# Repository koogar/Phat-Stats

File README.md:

Phat-Stats is an open-source Arduino project that transforms a TFT display into a real-time PC hardware performance monitor. Developed by Rupert Hirst and Colin Conway, it serves as a larger, color-enhanced counterpart to the Gnat-Stats OLED monitor, offering a visually rich interface for tracking system metrics.([GitHub][1], [GitHub][2])

---

### 🔧 Features

* **Real-Time Monitoring**: Displays key PC performance metrics such as CPU usage, temperatures, and more.
* **TFT Display Support**: Designed for ILI9341 TFT screens, providing a vibrant and detailed visual output.
* **Arduino Compatibility**: Supports various Arduino-compatible boards, including ESP32 and Seeeduino XIAO.
* **Windows Integration**: Utilizes the HardwareSerialMonitor Windows client to fetch and transmit system data via USB serial communication.([GitHub][1], [GitHub][3], [GitHub][4])

---

### 🛠️ Getting Started

1. **Hardware Setup**:

   * Connect an ILI9341 TFT display to your chosen Arduino-compatible board.
   * For detailed setup guides and tutorials, refer to the [Phat-Stats ILI9341 TFT Display Hook-Up Guide](https://runawaybrainz.blogspot.com/2021/03/phat-stats-ili9341-tft-display-hook-up.html).
    
2. **Software Installation**:

   * Flash the appropriate Phat-Stats firmware onto your microcontroller.
   * Install the [HardwareSerialMonitor](https://github.com/koogar/HardwareSerialMonitor) on your Windows PC to relay performance data.
3. **Configuration**:

   * Adjust settings within the Phat-Stats firmware and HardwareSerialMonitor to match your hardware setup and monitoring preferences.

---

### 📦 Repository Contents

* **Firmware Variants**:

  * `PhatStats_ESP32_LOLIN`: For ESP32-based boards.
  * `PhatStats_XIAO_QT-PY_WIO`: Tailored for Seeeduino XIAO and similar boards.

* **Documentation**:

  * `README.md`: Project overview and setup instructions.
  * `LICENSE.txt`: GPL v2 license details.([GitHub][1], [GitHub][3], [GitHub][2])

---

### 📄 License

Phat-Stats is released under the GNU General Public License v2.0. You are free to use, modify, and distribute this software in accordance with the license terms.

---

### 🔗 Additional Resources

* **Project Blog**: [Runaway Brainz](http://runawaybrainz.blogspot.com/)
* **Developer Site**: [Tallman Labs](http://tallmanlabs.com)
* **Related Projects**:

  * [Gnat-Stats](https://github.com/koogar/Gnat-Stats): A compact OLED-based performance monitor.
  * [Tacho-Stats](https://github.com/koogar/Tacho-Stats): Designed for Seeed Studio Round Displays.([GitHub][5], [GitHub][2], [GitHub][3])

---

For detailed setup guides and tutorials, refer to the [Phat-Stats ILI9341 TFT Display Hook-Up Guide](https://runawaybrainz.blogspot.com/2021/03/phat-stats-ili9341-tft-display-hook-up.html).

---

[1]: https://github.com/koogar/Phat-Stats?utm_source=chatgpt.com "GitHub - koogar/Phat-Stats: TFT Arduino PC Hardware Performance Serial ..."
[2]: https://github.com/koogar/Gnat-Stats?utm_source=chatgpt.com "GitHub - koogar/Gnat-Stats: GnatStats Tiny OLED Arduino PC Hardware ..."
[3]: https://github.com/koogar/Tacho-Stats?utm_source=chatgpt.com "GitHub - koogar/Tacho-Stats: PC Hardware Performance Monitor for the ..."
[4]: https://github.com/koogar/HardwareSerialMonitor?utm_source=chatgpt.com "GitHub - koogar/HardwareSerialMonitor: PC Performance Stats Serial ..."
[5]: https://github.com/koogar?utm_source=chatgpt.com "koogar (Tallman Labs) - GitHub"

  #GNATSTATS OLED, PHATSTATS TFT PC Performance Monitor & HardwareSerialMonitor Windows Client  
   Rupert Hirst & Colin Conway © 2016-2025

 http://tallmanlabs.com
 http://runawaybrainz.blogspot.com/  
 https://hackaday.io/project/19018-phat-stats-pc-performance-tft-display

# Phat-Stats TFT
 Arduino PC Hardware Performance Serial Display
Phat-Stats ILI9341 TFT

https://runawaybrainz.blogspot.com/2021/03/phat-stats-ili9341-tft-display-hook-up.html

.jpg)

.jpg)

  Licence
  -------
  
  GPL v2
  
Gnat-Stats, Phat-Stats, Tacho-Stats, uVolume & HardwareSerialMonitor
Copyright (C) 2016 -2025  Colin Conway, Rupert Hirst and contributors
 
This program is free software; you can redistribute it and/or
modify it under the terms of the GNU General Public License
as published by the Free Software Foundation; either version 2
of the License, or (at your option) any later version.

This program is distributed in the hope that it will be useful,
but WITHOUT ANY WARRANTY; without even the implied warranty of
MERCHANTABILITY or FITNESS FOR A PARTICULAR PURPOSE.  See the
GNU General Public License for more details.

You should have received a copy of the GNU General Public License
along with this program; If not, see <http://www.gnu.org/licenses/>.

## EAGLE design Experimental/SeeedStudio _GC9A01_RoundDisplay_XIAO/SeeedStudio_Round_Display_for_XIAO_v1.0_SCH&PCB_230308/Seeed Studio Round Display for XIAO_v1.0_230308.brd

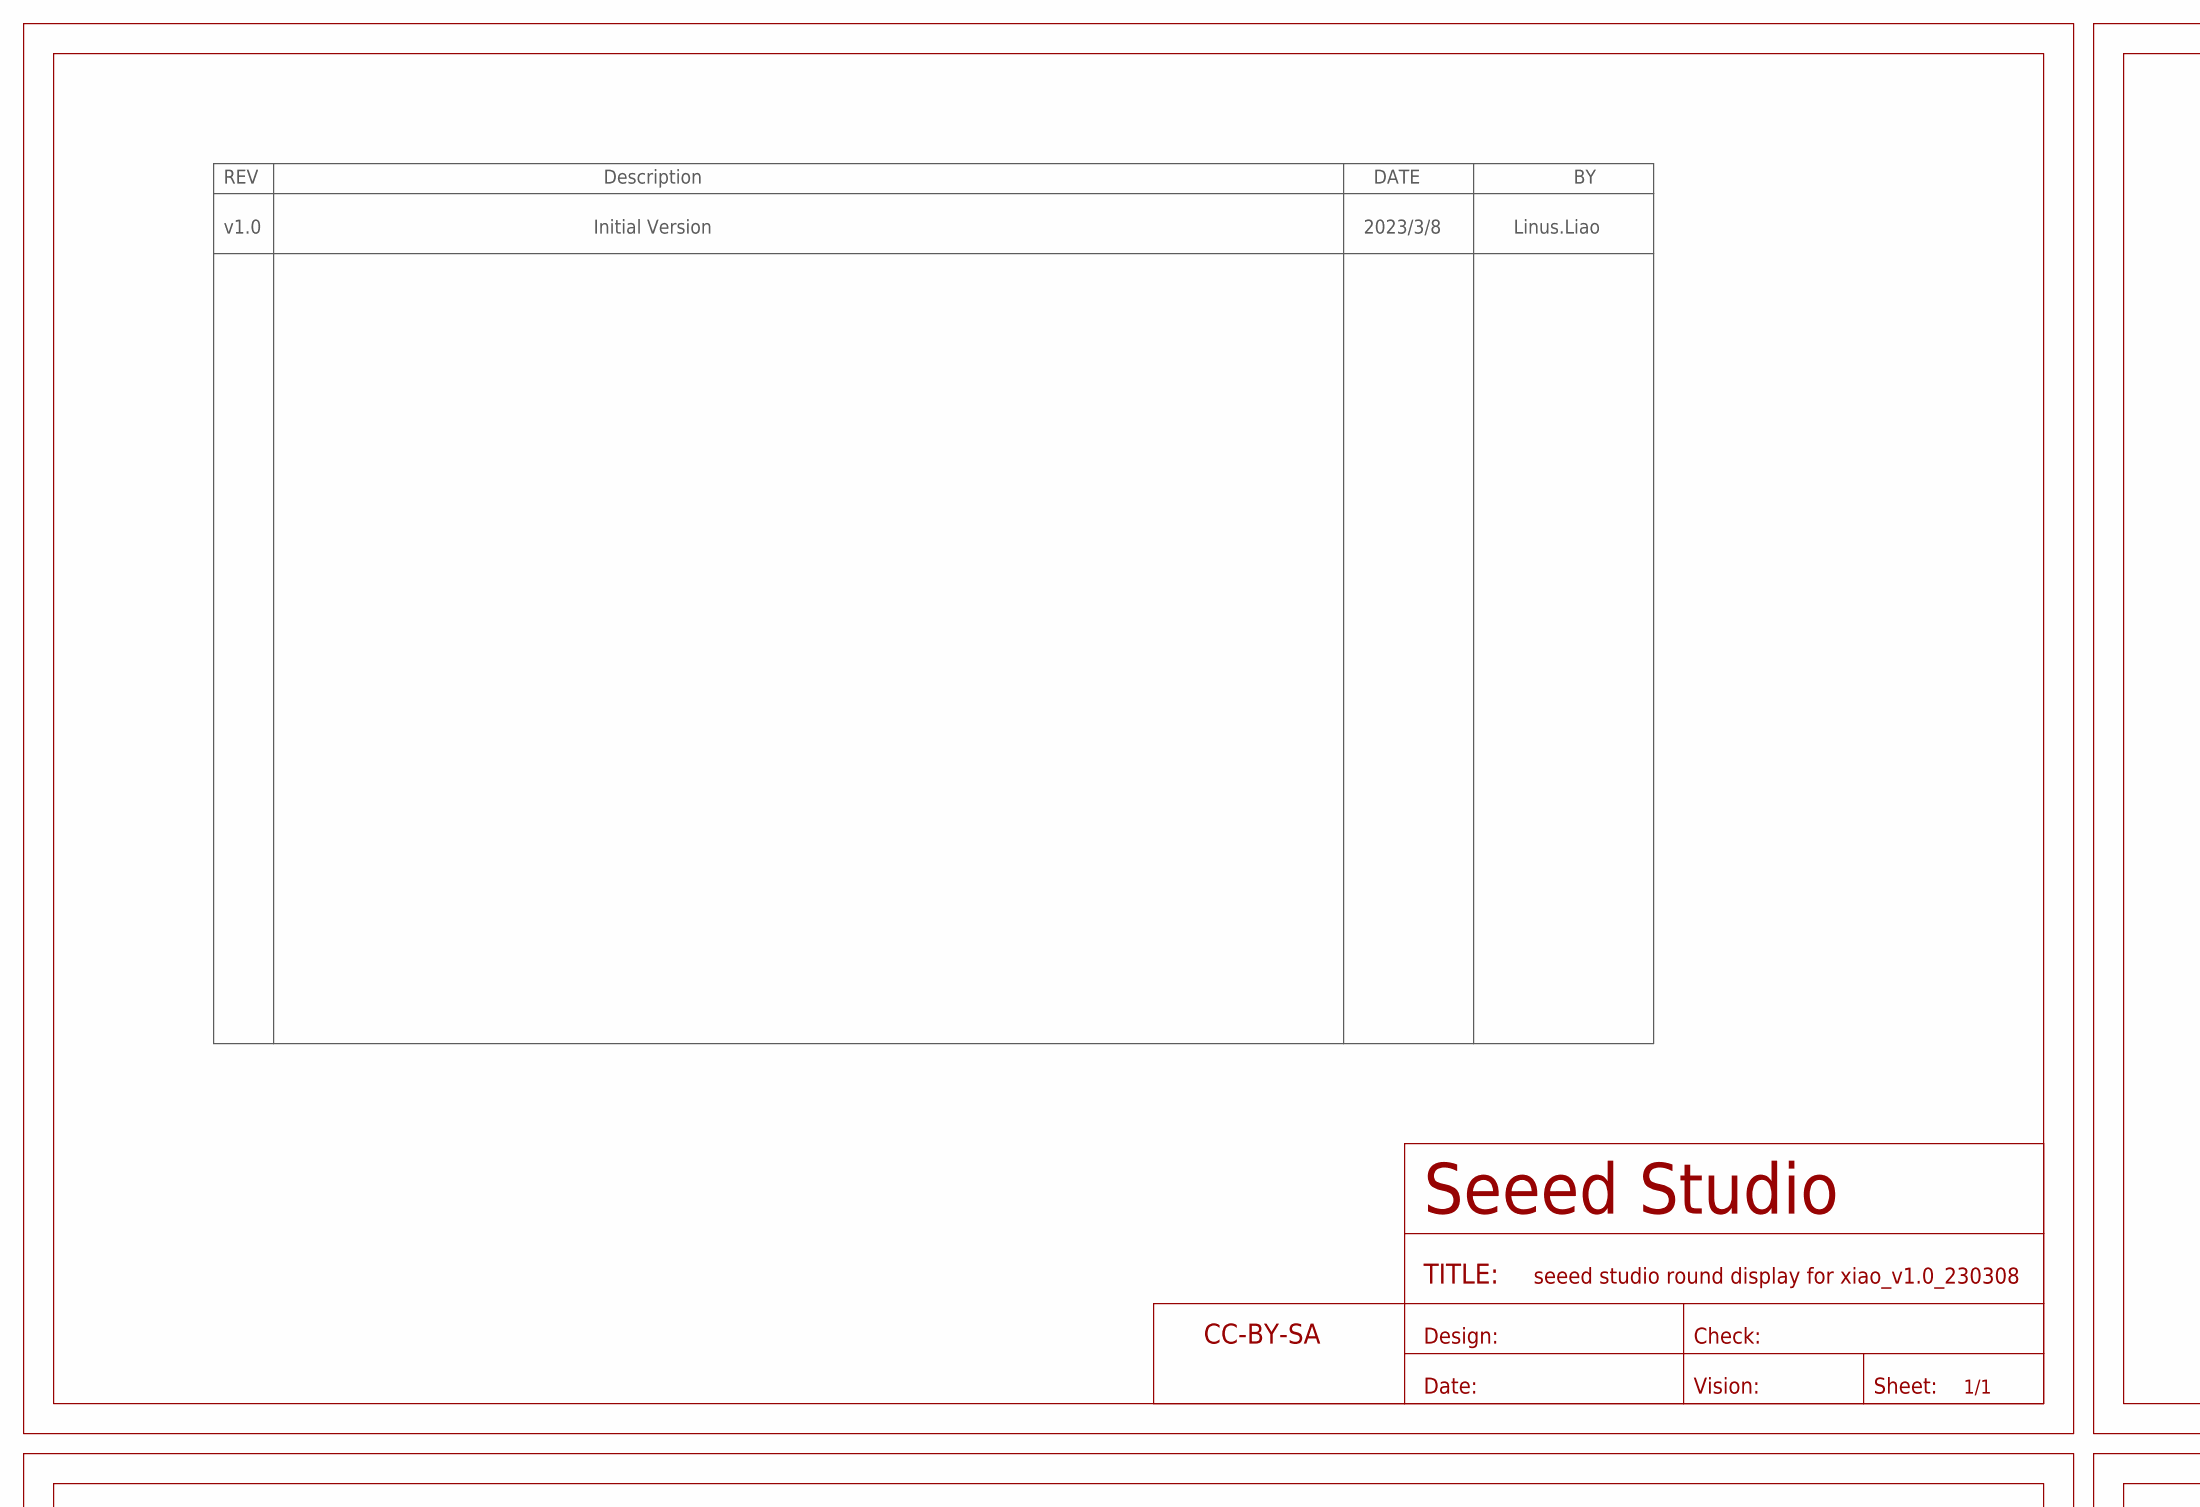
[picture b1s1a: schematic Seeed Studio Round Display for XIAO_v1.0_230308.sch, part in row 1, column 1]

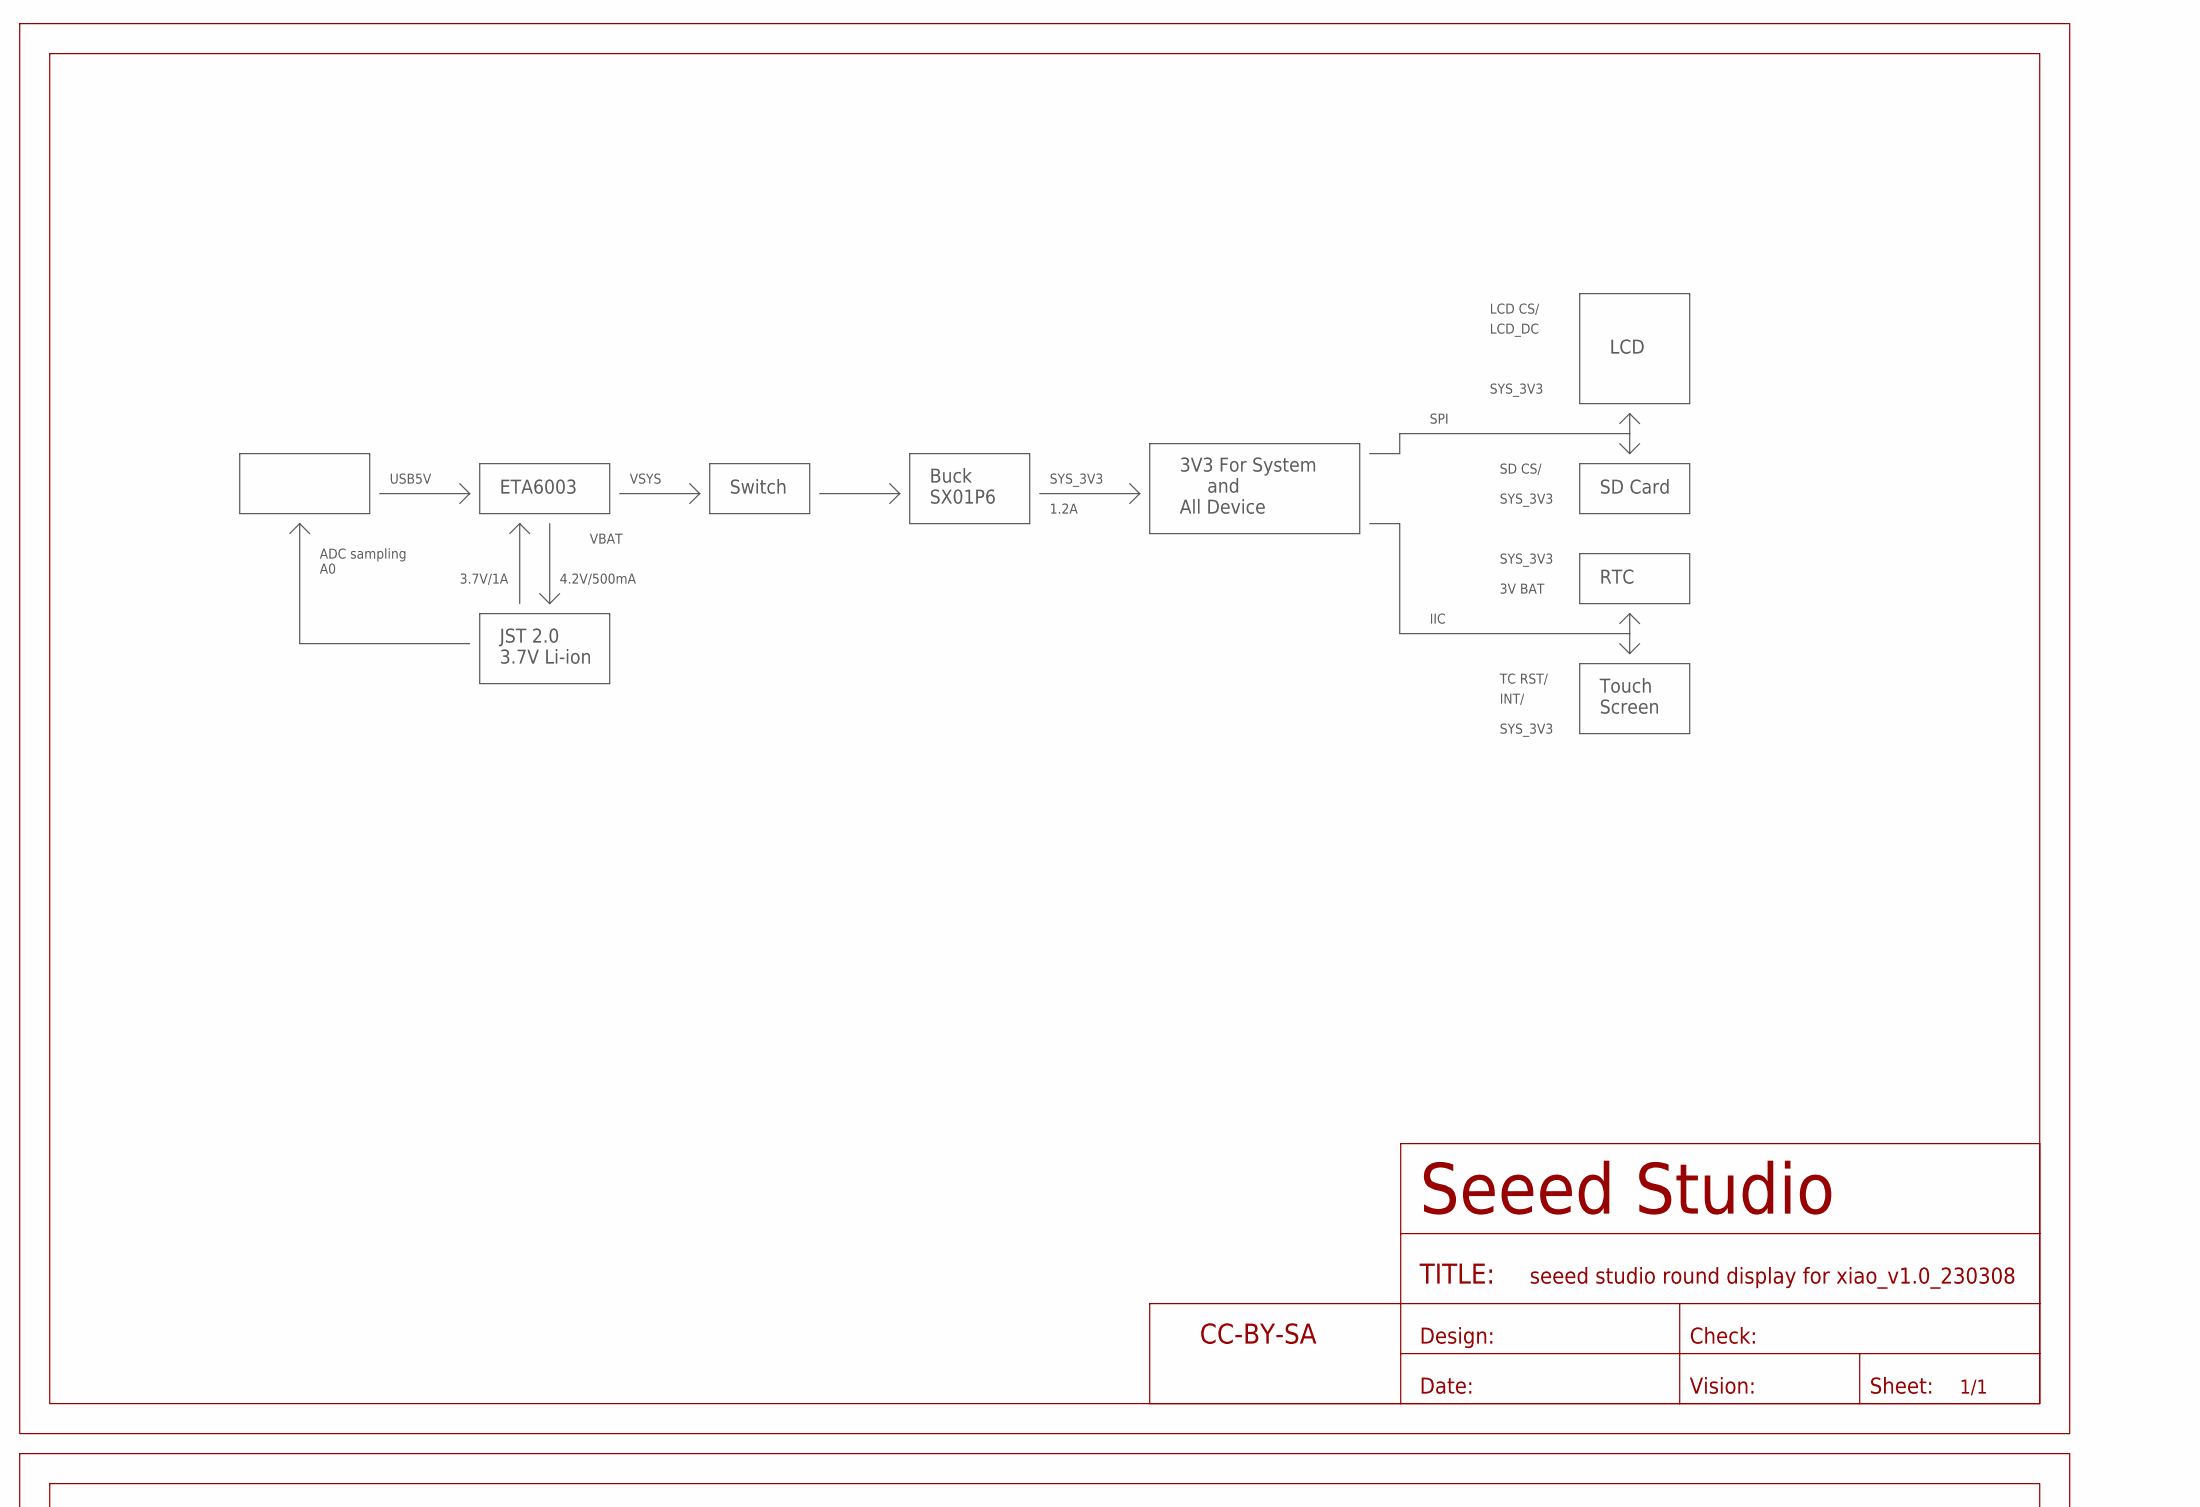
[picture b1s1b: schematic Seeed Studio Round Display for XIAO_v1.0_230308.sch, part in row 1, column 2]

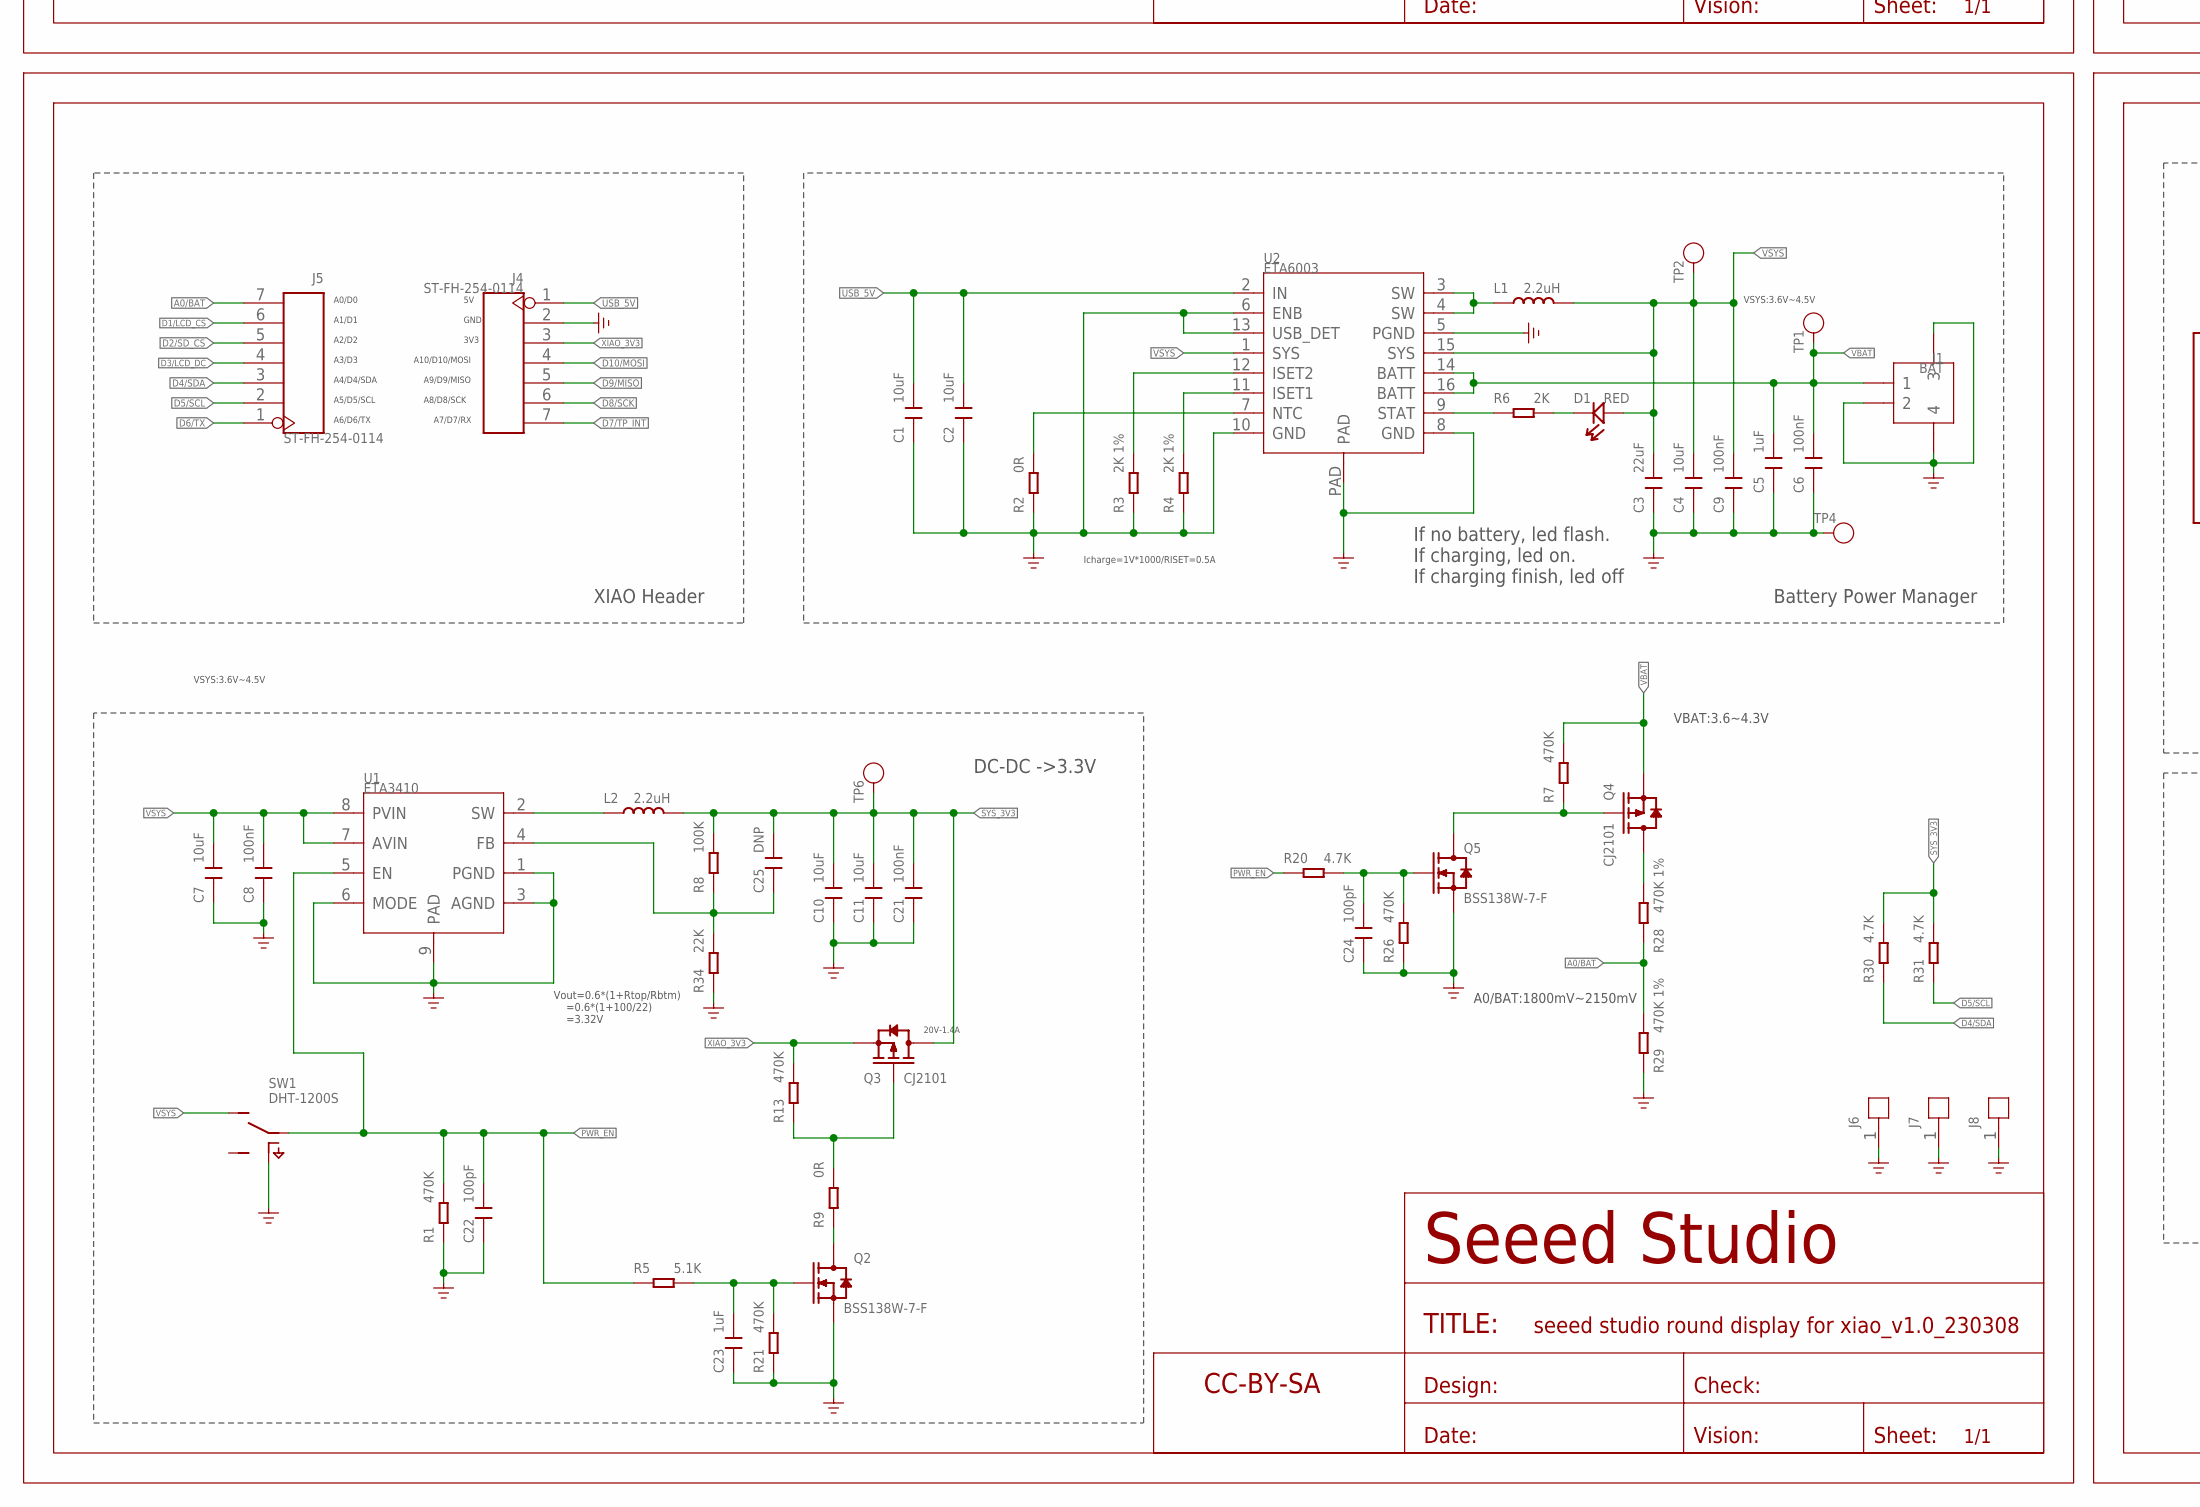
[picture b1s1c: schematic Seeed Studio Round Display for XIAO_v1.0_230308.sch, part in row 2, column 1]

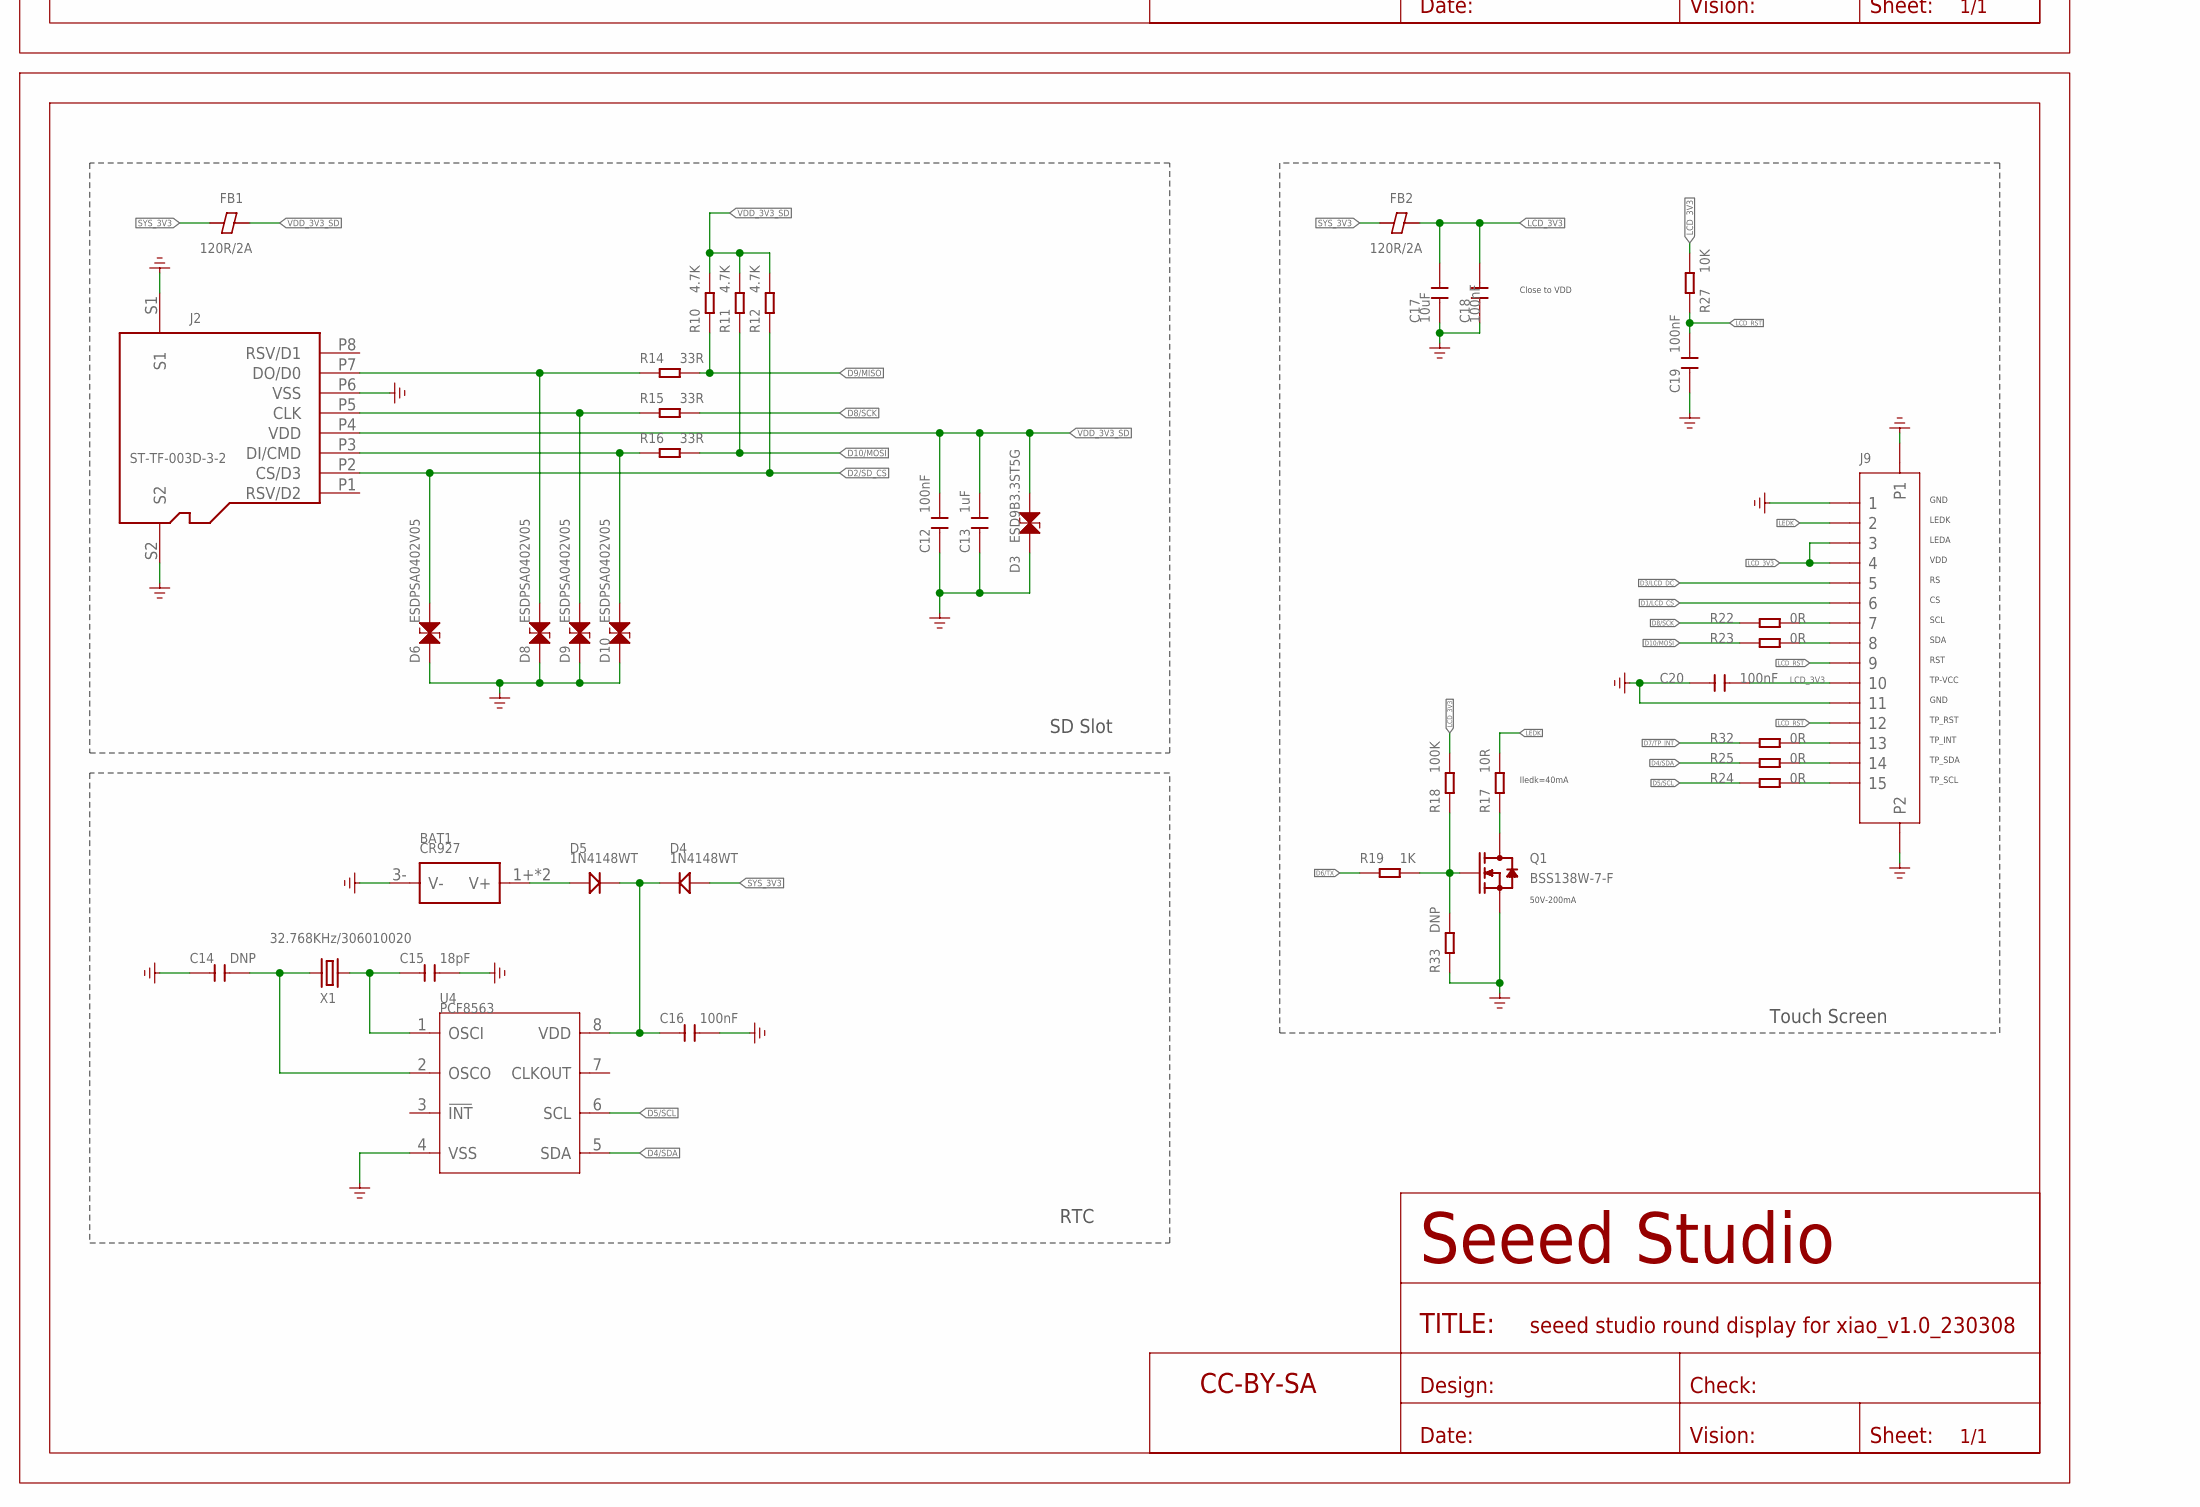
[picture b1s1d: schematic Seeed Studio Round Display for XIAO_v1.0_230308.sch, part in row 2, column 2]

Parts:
BAT1: CR927; BAT2P-SMD-15.3X8.6X2.9MM
C1, C2, C4, C7, C10, C11: 10uF; C0603
C3: 22uF; C0603
C5, C13, C23: 1uF; C0402
C6, C8, C9, C12, C16, C18, C19, C20, C21: 100nF; C0402
C14, C25: DNP; C0402
C15: 18pF; C0402
C17: 10uF; C0402
C22, C24: 100pF; C0402
D1: RED; LED-0402
D3: ESD9B3.3ST5G; ESD-0402
D4, D5: 1N4148WT; SOD-523
D6, D8, D9, D10: ESDPSA0402V05; ESD-0402
FB1, FB2: 120R/2A; F0402
FR1, FR2, FR3, FR4: SEEEDSTUDIO-OPEN-SCH-FRAME; SEEEDSTUDIO-PCB-FRAME
J1: BAT; HW2+2P-SMD-1.25
J2: ST-TF-003D-3-2; MICRO-SD8+2P-SMD-1.1-11.41X4.9X3MM
J4, J5: ST-FH-254-0114; H7-2.54-18.28X2.5X5MM
J6, J7, J8: HEADER-1P-3.5/2.2_PASTE; H1P-3.5/2.2MM-PASTE
J9: FPC-CONNECTOR-15P; FPC15P-0.6-6.1X2.83X1MM
L1, L2: 2.2uH; L0806
Q1, Q2, Q5: BSS138W-7-F; SOT-323
Q3, Q4: CJ2101; SOT-323
R1, R7, R13, R21, R26: 470K; R0402
R2, R9, R22, R23, R24, R25, R32: 0R; R0402
R3, R4: 2K 1%; R0402
R5: 5.1K; R0402
R6: 2K; R0402
R8, R18: 100K; R0402
R10, R11, R12, R20, R30, R31: 4.7K; R0402
R14, R15, R16: 33R; R0402
R17: 10R; R0603
R19: 1K; R0402
R27: 10K; R0402
R28, R29: 470K 1%; R0402
R33: DNP; R0402
R34: 22K; R0402
SW1: DHT-1200S; SW7-SMD-6.7X2.6X1.4MM-90D
TP1, TP2, TP4, TP6: TEST-POINT'4545'; TP-D45MIL
U1: ETA3410; DFN8G-0.5-2X2MM
U2: ETA6003; QFN16GA-0.5-3X3MM
U4: PCF8563; SOP8-1.27-5X3.9MM
X1: 32.768KHz/306010020; X2-SMD-L2.0X1.2X0.55MM

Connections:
A0/BAT: J5.7, R28.1, R29.2
D1/LCD_CS: J5.6, J9.6
D2/SD_CS: D6.2, J2.P2 (CS/D3), J5.5, R12.1
D3/LCD_DC: J5.4, J9.5
D4/SDA: J5.3, R25.1, R30.1, U4.5 (SDA)
D5/SCL: J5.2, R24.1, R31.1, U4.6 (SCL)
D6/TX: J5.1, R19.1
D7/TP_INT: J4.7, R32.1
D8/SCK: J4.6, R15.2, R22.1
D9/MISO: J4.5, R10.1, R14.2
D10/MOSI: J4.4, R11.1, R16.2, R23.1
GND: BAT1.3- (V-), C1.1, C2.1, C3.1, C4.1, C5.1, C6.1, C7.1, C8.1, C9.1, C10.1, C11.1, C12.1, C13.1, C14.1, C15.2, C16.2, C17.1, C18.1, C19.1, C20.1, C21.1, C22.1, C23.1, C24.1, D3.1, D6.1, D8.1, D9.1, D10.1, J1.2, J1.P1 (3), J1.P2 (4), J2.P6 (VSS), J2.S1, J2.S2, J4.2, J6.1, J7.1, J8.1, J9.1, J9.11, J9.16 (P1), J9.17 (P2), Q1.2 (S), Q2.2 (S), Q5.2 (S), R1.1, R2.1, R3.1, R4.1, R21.1, R26.1, R29.1, R33.1, R34.1, SW1.P1 (SS2), SW1.P2 (SS2), SW1.P3 (SS2), SW1.P4 (SS2), TP4.T, U1.1 (PGND), U1.3 (AGND), U1.6 (MODE), U1.9 (PAD), U2.5 (PGND), U2.6 (ENB), U2.8 (GND), U2.10 (GND), U2.13 (USB_DET), U2.PAD, U4.4 (VSS)
LCD_3V3: C17.2, C18.2, C20.2, FB2.2, J9.3, J9.4, J9.10, R18.2, R27.2
LCD_RST: C19.2, J9.9, J9.12, R27.1
LEDK: J9.2, R17.2
unnamed: R6.1, U2.9 (STAT)
unnamed: J9.13, R32.2
unnamed: R2.2, U2.7 (NTC)
unnamed: C25.1, R8.1, R34.2, U1.4 (FB)
unnamed: R3.2, U2.12 (ISET2)
unnamed: R4.2, U2.11 (ISET1)
unnamed: D1.-, R6.2
unnamed: Q4.3 (D), R28.2
unnamed: L1.1, U2.3 (SW), U2.4 (SW)
unnamed: C23.2, Q2.1 (G), R5.2, R21.2
unnamed: L2.1, U1.2 (SW)
unnamed: Q4.1 (G), Q5.3 (D), R7.1
unnamed: Q3.1 (G), R9.2, R13.1
unnamed: C14.2, U4.2 (OSCO), X1.1
unnamed: Q2.3 (D), R9.1
unnamed: D8.2, J2.P7 (DO/D0), R14.1
unnamed: D9.2, J2.P5 (CLK), R15.1
unnamed: D10.2, J2.P3 (DI/CMD), R16.1
unnamed: C15.1, U4.1 (OSCI), X1.2
unnamed: Q1.1 (G), R18.1, R19.2, R33.2
unnamed: J9.7, R22.2
unnamed: Q1.3 (D), R17.1
unnamed: C16.1, D4.-, D5.-, U4.8 (VDD)
unnamed: J9.8, R23.2
unnamed: BAT1.1+ (V+), BAT1.2+ (V+), D5.+
unnamed: C24.2, Q5.1 (G), R20.2, R26.2
unnamed: J9.14, R25.2
unnamed: J9.15, R24.2
PWR_EN: C22.2, R1.2, R5.1, R20.1, SW1.2 (COM), U1.5 (EN)
SYS_3V3: C10.2, C11.2, C21.2, C25.2, D4.+, FB1.1, FB2.1, L2.2, Q3.3 (D), R8.2, R30.2, R31.2, TP6.T
USB_5V: C1.2, C2.2, J4.1, U2.2 (IN)
VBAT: C5.2, C6.2, J1.1, Q4.2 (S), R7.2, TP1.T, U2.14 (BATT), U2.16 (BATT)
VDD_3V3_SD: C12.2, C13.2, D3.2, FB1.2, J2.P4 (VDD), R10.2, R11.2, R12.2
VSYS: C3.2, C4.2, C7.2, C8.2, C9.2, D1.+, L1.2, SW1.1 (A), TP2.T, U1.7 (AVIN), U1.8 (PVIN), U2.1 (SYS), U2.15 (SYS)
XIAO_3V3: J4.3, Q3.2 (S), R13.2

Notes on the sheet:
ETA6003
USB5V
JST 2.0 3.7V Li-ion
Buck SX01P6
Switch
VSYS
SYS_3V3
3V3 For System and All Device
LCD
RTC
SD Card
VBAT
4.2V/500mA
3.7V/1A
ADC sampling A0
1.2A
SPI
LCD CS/
LCD_DC
SD CS/
Touch Screen
IIC
TC RST/
INT/
3V BAT
v1.0
Initial Version
Linus.Liao
Icharge=1V*1000/RISET=0.5A
VSYS:3.6V~4.5V
If no battery, led flash. If charging, led on. If charging finish, led off
VBAT:3.6~4.3V
A0/BAT:1800mV~2150mV
SD Slot
Touch Screen
Battery Power Manager
DC-DC ->3.3V
GND
LEDK
LEDA

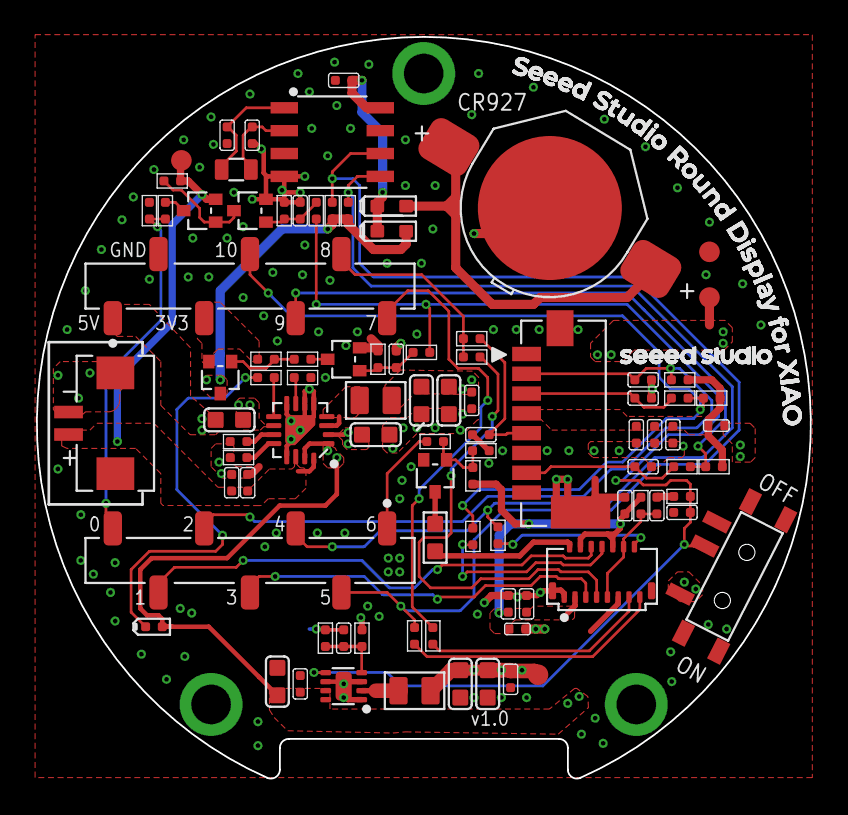
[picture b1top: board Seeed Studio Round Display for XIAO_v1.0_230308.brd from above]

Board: 2 copper layers, 43.0 x 41.2 mm, 99 parts (0 on the bottom side), 50 nets.

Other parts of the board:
U$1: LOGO-SEEED-NEW-0.94X8.4MM

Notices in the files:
Experimental/PhatStats_MULTI-MCU_XIAO_QT-PY_WIO_V3.1.2_ADV_Flipped/PhatStats_MULTI-MCU_XIAO_QT-PY_WIO_V3.1.2_ADV_Flipped.ino:
Rupert Hirst & Colin Conway © 2016 - 2021
GPL v2
PhatStats_TFT_STM32F1_V1.6.5.9.4/PhatStats_TFT_STM32F1_V1.6.5.9.4.ino:
Rupert Hirst & Colin Conway © 2016 - 2018
parts and their libraries:
SparkFun-Switches: Licensing: Creative Commons ShareAlike 4.0 International - https://creativecommons.org/licenses/by-sa/4.0
moudle-new: This work is licensed under the Creative Commons Attribution 4.0 International License.
To view a copy of this license,visit: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
moudle-new: CC-BY-SA
